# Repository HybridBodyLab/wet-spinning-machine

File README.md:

# wet-spinning-machine

## Documentation Website
[hybridbodylab.github.io/open-wet-spinning](https://hybridbodylab.github.io/open-wet-spinning/)

## License

This project is open source and freely available under the following licenses:

- **Hardware designs** (PCBs, 3D-printable parts): [CERN-OHL-P v2.0](https://ohwr.org/project/cernohl/wikis/home)
- **Firmware**: [MIT License](https://opensource.org/licenses/MIT)
- **Documentation and media**: [Creative Commons Attribution 4.0 (CC BY 4.0)](https://creativecommons.org/licenses/by/4.0/)

You are free to use, modify, and distribute this project, provided that you give appropriate credit to the original author.

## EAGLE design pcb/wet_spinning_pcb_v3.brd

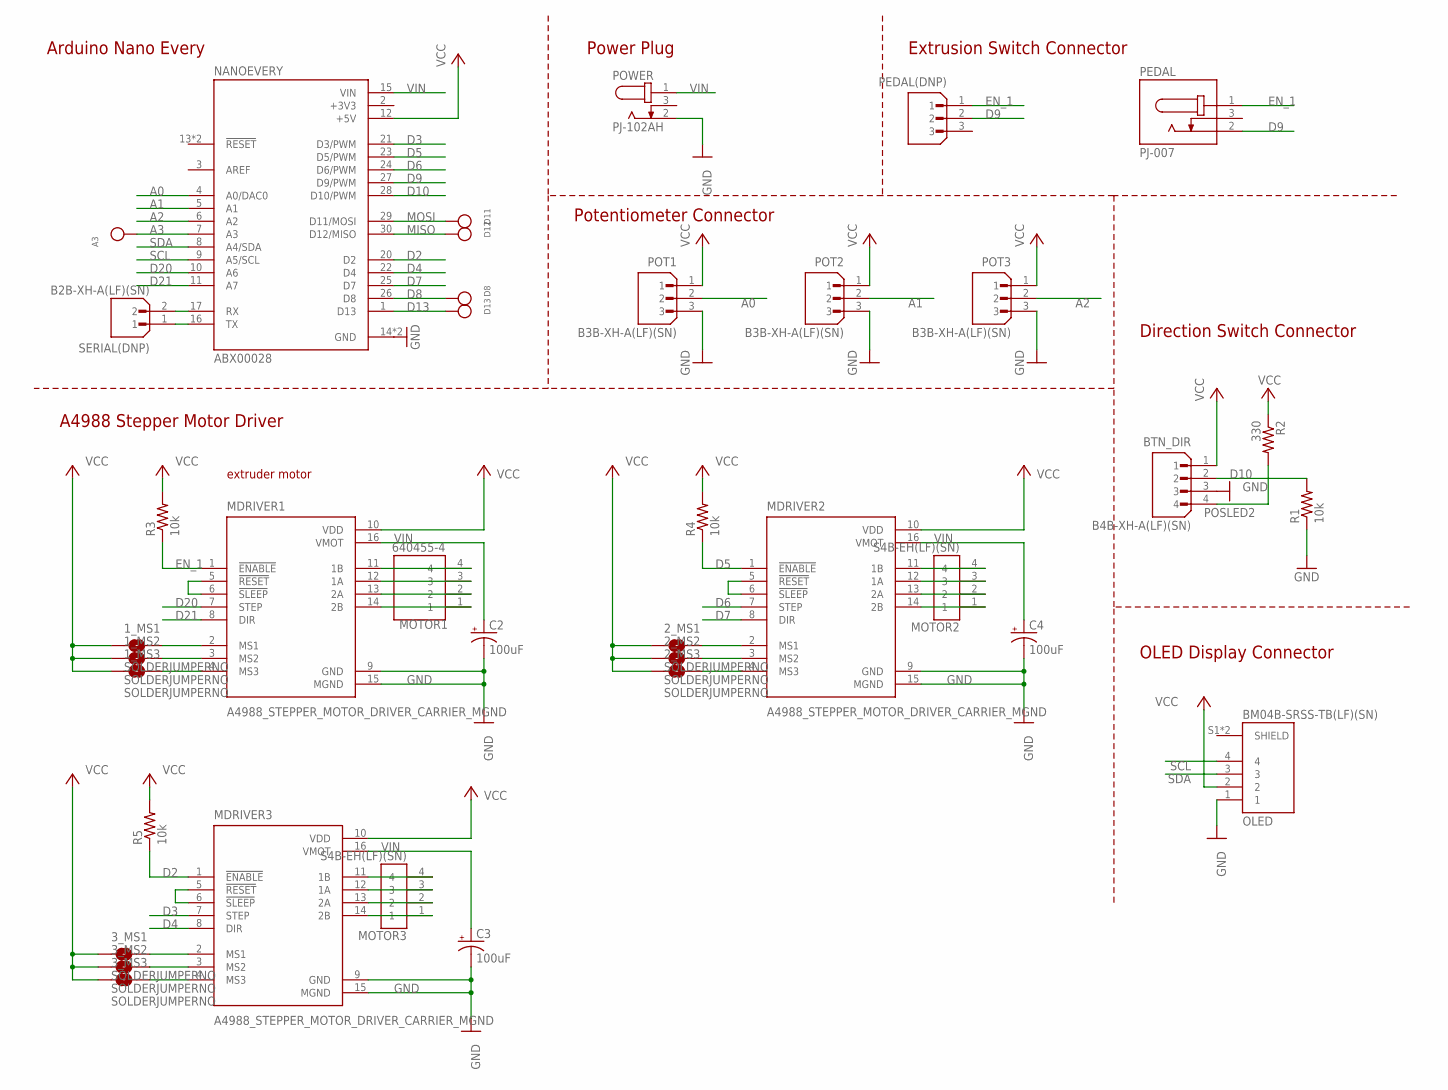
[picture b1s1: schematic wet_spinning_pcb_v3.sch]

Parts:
1_MS1, 1_MS2, 1_MS3, 2_MS1, 2_MS2, 2_MS3, 3_MS1, 3_MS2, 3_MS3: SOLDERJUMPERNO; SJ_2S-NO
A3: TESTPOINT0.1"; 1X01_ROUND
BTN_DIR: B4B-XH-A(LF)(SN); JST_B4B-XH-A(LF)(SN)
C2, C3, C4: 100uF; CPOL-RADIAL-2.5MM-6.5MM
D8, D11, D12, D13: TESTPOINT0.1"; 1X01_ROUND
MDRIVER1, MDRIVER2, MDRIVER3: A4988_STEPPER_MOTOR_DRIVER_CARRIER_MGND; MODULE_A4988_STEPPER_MOTOR_DRIVER_CARRIER
MOTOR1: 640455-4; TE_640455-4
MOTOR2, MOTOR3: S4B-EH(LF)(SN); JST_S4B-EH(LF)(SN)
NANOEVERY: ABX00028; MODULE_ABX00028
OLED: BM04B-SRSS-TB(LF)(SN); JST_BM04B-SRSS-TB(LF)(SN)
PEDAL: PJ-007; CUI_PJ-007
PEDAL(DNP): B3B-XH-A(LF)(SN); JST_B3B-XH-A(LF)(SN)
POT1, POT2, POT3: B3B-XH-A(LF)(SN); JST_B3B-XH-A(LF)(SN)
POWER: PJ-102AH; CUI_PJ-102AH
R1, R3, R4, R5: 10k; 0204/7
R2: 330; 0204/7
SERIAL(DNP): B2B-XH-A(LF)(SN); JST_B2B-XH-A(LF)(SN)

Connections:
+3V3: NANOEVERY.2 (+3V3)
A0: NANOEVERY.4 (A0/DAC0), POT1.2
A1: NANOEVERY.5 (A1), POT2.2
A2: NANOEVERY.6 (A2), POT3.2
A3: A3.1, NANOEVERY.7 (A3)
D2: MDRIVER3.1 (!ENABLE), NANOEVERY.20 (D2), R5.1
D3: MDRIVER3.7 (STEP), NANOEVERY.21 (D3/PWM)
D4: MDRIVER3.8 (DIR), NANOEVERY.22 (D4)
D5: MDRIVER2.1 (!ENABLE), NANOEVERY.23 (D5/PWM), R4.1
D6: MDRIVER2.7 (STEP), NANOEVERY.24 (D6/PWM)
D7: MDRIVER2.8 (DIR), NANOEVERY.25 (D7)
D8: D8.1, NANOEVERY.26 (D8)
D9: NANOEVERY.27 (D9/PWM), PEDAL.2, PEDAL(DNP).2
D10: BTN_DIR.2, NANOEVERY.28 (D10/PWM), R1.2
D13: D13.1, NANOEVERY.1 (D13)
D20: MDRIVER1.7 (STEP), NANOEVERY.10 (A6)
D21: MDRIVER1.8 (DIR), NANOEVERY.11 (A7)
EN_1: MDRIVER1.1 (!ENABLE), PEDAL.1, PEDAL(DNP).1, R3.1
GND: BTN_DIR.3, C2.2 (-), C3.2 (-), C4.2 (-), MDRIVER1.9 (GND), MDRIVER1.15 (MGND), MDRIVER2.9 (GND), MDRIVER2.15 (MGND), MDRIVER3.9 (GND), MDRIVER3.15 (MGND), NANOEVERY.14 (GND), NANOEVERY.19 (GND), OLED.1, POT1.3, POT2.3, POT3.3, POWER.2, R1.1
MISO: D12.1, NANOEVERY.30 (D12/MISO)
MOSI: D11.1, NANOEVERY.29 (D11/MOSI)
unnamed: MDRIVER1.12 (1A), MOTOR1.3
unnamed: MDRIVER1.11 (1B), MOTOR1.4
unnamed: MDRIVER3.14 (2B), MOTOR3.1
unnamed: MDRIVER3.13 (2A), MOTOR3.2
unnamed: MDRIVER1.5 (!RESET), MDRIVER1.6 (!SLEEP)
unnamed: MDRIVER3.5 (!RESET), MDRIVER3.6 (!SLEEP)
unnamed: MDRIVER2.5 (!RESET), MDRIVER2.6 (!SLEEP)
unnamed: 1_MS1.2, MDRIVER1.2 (MS1)
unnamed: MDRIVER1.14 (2B), MOTOR1.1
unnamed: MDRIVER1.13 (2A), MOTOR1.2
unnamed: 1_MS2.2, MDRIVER1.3 (MS2)
unnamed: 1_MS3.2, MDRIVER1.4 (MS3)
unnamed: MDRIVER3.12 (1A), MOTOR3.3
unnamed: MDRIVER3.11 (1B), MOTOR3.4
unnamed: MDRIVER2.14 (2B), MOTOR2.1
unnamed: MDRIVER2.13 (2A), MOTOR2.2
unnamed: MDRIVER2.12 (1A), MOTOR2.3
unnamed: MDRIVER2.11 (1B), MOTOR2.4
unnamed: NANOEVERY.16 (TX), SERIAL(DNP).1
unnamed: NANOEVERY.17 (RX), SERIAL(DNP).2
unnamed: 2_MS1.2, MDRIVER2.2 (MS1)
unnamed: 2_MS2.2, MDRIVER2.3 (MS2)
unnamed: 2_MS3.2, MDRIVER2.4 (MS3)
unnamed: 3_MS1.2, MDRIVER3.2 (MS1)
unnamed: 3_MS2.2, MDRIVER3.3 (MS2)
unnamed: 3_MS3.2, MDRIVER3.4 (MS3)
POSLED2: BTN_DIR.4, R2.2
SCL: NANOEVERY.9 (A5/SCL), OLED.4
SDA: NANOEVERY.8 (A4/SDA), OLED.3
VCC: 1_MS1.1, 1_MS2.1, 1_MS3.1, 2_MS1.1, 2_MS2.1, 2_MS3.1, 3_MS1.1, 3_MS2.1, 3_MS3.1, BTN_DIR.1, MDRIVER1.10 (VDD), MDRIVER2.10 (VDD), MDRIVER3.10 (VDD), NANOEVERY.12 (+5V), OLED.2, POT1.1, POT2.1, POT3.1, R2.1, R3.2, R4.2, R5.2
VIN: C2.1 (+), C3.1 (+), C4.1 (+), MDRIVER1.16 (VMOT), MDRIVER2.16 (VMOT), MDRIVER3.16 (VMOT), NANOEVERY.15 (VIN), POWER.1

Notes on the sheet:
Arduino Nano Every
A4988 Stepper Motor Driver
Extrusion Switch Connector
OLED Display Connector
Direction Switch Connector
Potentiometer Connector
Power Plug
extruder motor

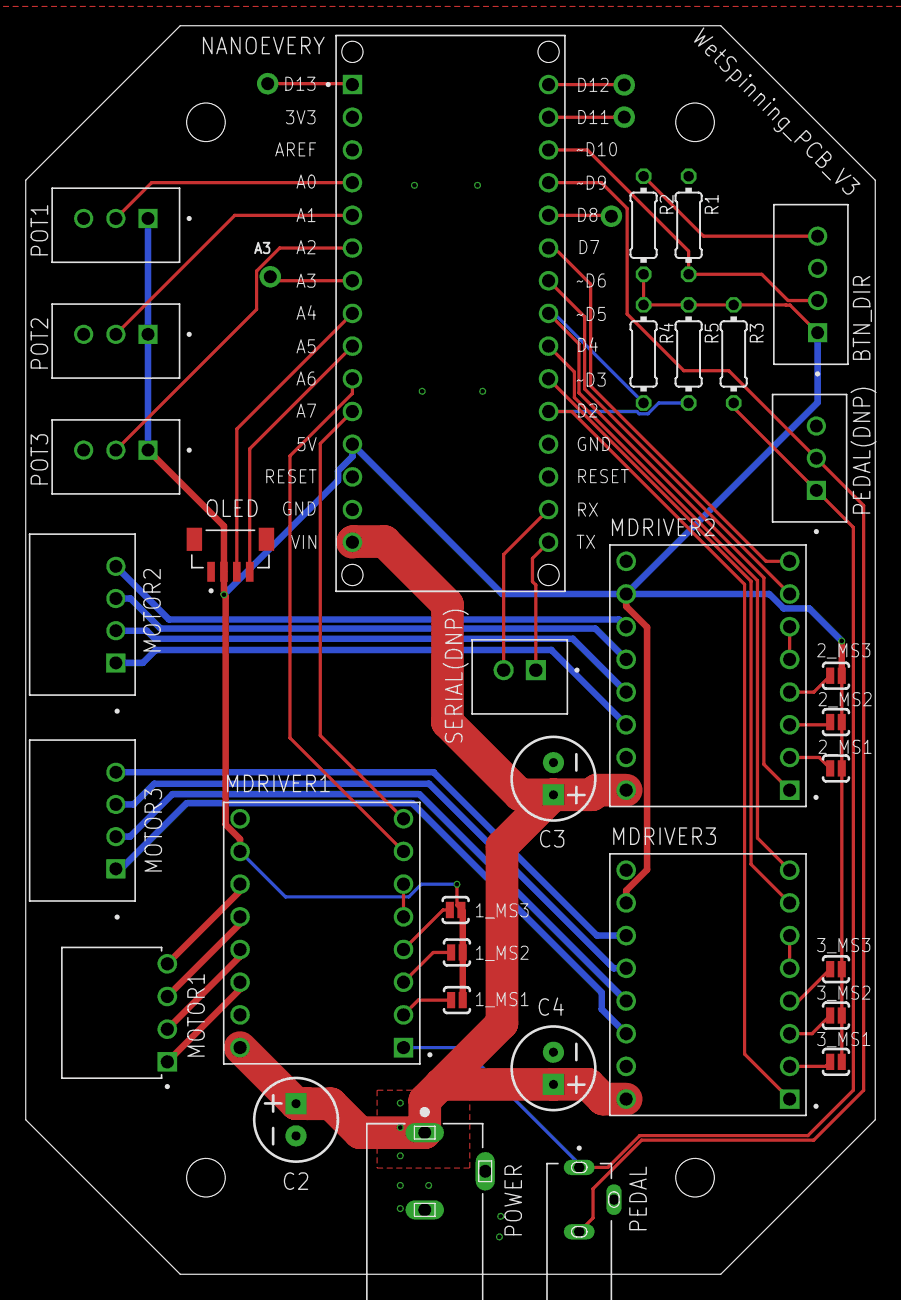
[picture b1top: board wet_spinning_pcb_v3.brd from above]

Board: 2 copper layers, 66.0 x 97.0 mm, 38 parts (0 on the bottom side), 51 nets.

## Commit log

2025-04-15 init folder structure
2025-04-15 added stl files and openscad files
2025-04-15 added openscad files
2025-04-15 added pcb design and arduino code
2025-04-16 Updated arduino comments
2025-04-22 updated and renamed files
2025-06-26 Update README.md
    Updated website link

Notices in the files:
parts and their libraries:
SparkFun-Capacitors: Licensing: Creative Commons ShareAlike 4.0 International - https://creativecommons.org/licenses/by-sa/4.0
microbuilder: This work is placed in the public domain, and may be freely used for commercial and non-commercial work with the following conditions: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
